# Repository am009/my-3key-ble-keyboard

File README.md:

# 3key-bluetooth-mechanical-keyboard

Based on a tiny esp32 board TTGO T-Display. Draw a simple extension PCB with key switches for it. Connect with two row pins, and put battery in between.

基于TTGO T-Display这个小巧的开发板，通过排针排母连接一个带机械键盘轴的PCB，正好中间的位置放电池。本来打算放四个键，不太放得下就砍掉了一个键。

本项目的目的是学习使用Kicad，尝试画PCB，同时满足自己对小巧的蓝牙键盘的需求。没想到PCB双层板打样这么便宜，5块钱5张，那还用什么洞洞板，飞什么线，自己画拓展板去。这次拓展接线完全就是简单的IO口接轴接GND，甚至用esp32的内部上拉，走线甚至只用了单面。本来想尝试尝试esp_idf开发的，最后还是选择了Arduino IDE。。。比较简单。

Update:
 
- 休眠前主动断开连接，不必等到超时才断开 - ok
- 电量显示有时不稳定，会显示电量为0% - ok
- 低电量闪烁提醒。- 没有合适的板载led

## Reason
背anki用。三个键分别是Enter（good 绿色按钮）数字键1 (again 红色) 数字键2 (hard 灰色)
Make a small ble keyboard for Anki flashcards.
I mount my phone over my pillow, thinking about some way to control my phone. I tried using my Logitech bluethooth keyboard and feel great. When using Ankidroid to remember vocabularies, I found myself needing a tiny bluetooth keyboard.
the three key is set to Enter(for pressing the green(good) button), num 1(for red(again) button), and num 2(for gray(hard) button).

## Hardware

物料：

1. 电池最后选了~~802040（8mm厚，20mmx40mm） 800mah，勉强塞下~~(update 2021.9.13 前两天电池被键轴焊脚戳破了，改用602040锂电池)。续航能力7-10天。是1.25mm 2P 正向接口。 15元两个包邮
2. 买了4个cherry 茶轴和4个灰色键帽。 带邮费26。
3. TTGO T-Display 47元（带排针），加两个12P排母。
4. 自备烙铁焊锡丝。

能够自定义三个键，暂不支持复杂的宏操作。

TTGO自带的按键一个设置为查看电量，一个设置为休眠和开机。

可以自定义蓝牙显示的名称，能够通过蓝牙显示电量信息。

打样打了5块，只用了一块，可以联系我。

唤醒方面原本是通过三个键同时按下唤醒的，最后还是改成了屏幕下方的按钮休眠。

## PCB

PCB设计使用Kicad. 用了下面的组件

[tmk - keyboard_parts](https://github.com/tmk/keyboard_parts.pretty) 键轴

[ttgo_esp32](https://github.com/BravoRoot/ttgo-tdisplay-kicad) for ttgo t-display component.

[MX_Alps_Hybrid](https://github.com/ai03-2725/MX_Alps_Hybrid) 键轴

[ttgo t-display 3d model](https://grabcad.com/library/lilygo-ttgo-t-display-esp32-1) 可以测量尺寸

画PCB的时候为了保险就留了上拉电阻的位置，最后确实不用接。

## Firmware

最后选择了Arduino IDE开发。安装：

1. [Arduino 蓝牙键盘库](https://github.com/T-vK/ESP32-BLE-Keyboard) 
2. [TTGO的屏幕支持库](https://github.com/Xinyuan-LilyGO/TTGO-T-Display) 
3. 按照`Three_Key_TTGO\BleKeyboard.cpp.patch`和`Three_Key_TTGO\BleKeyboard.h.patch`修改ESP32-BLE-Keyboard库(为了支持即时断开连接)

开发板选择 ESP32 Dev Module,在PSRAM选项中选择Disable， Flash Size 选项中选择4MB ，其它保持默认

## TODO

1. 还是有外部上拉比较好，deep-sleep模式下负责内部上拉的RTC外设部分就可以休眠了。

## 图片展示

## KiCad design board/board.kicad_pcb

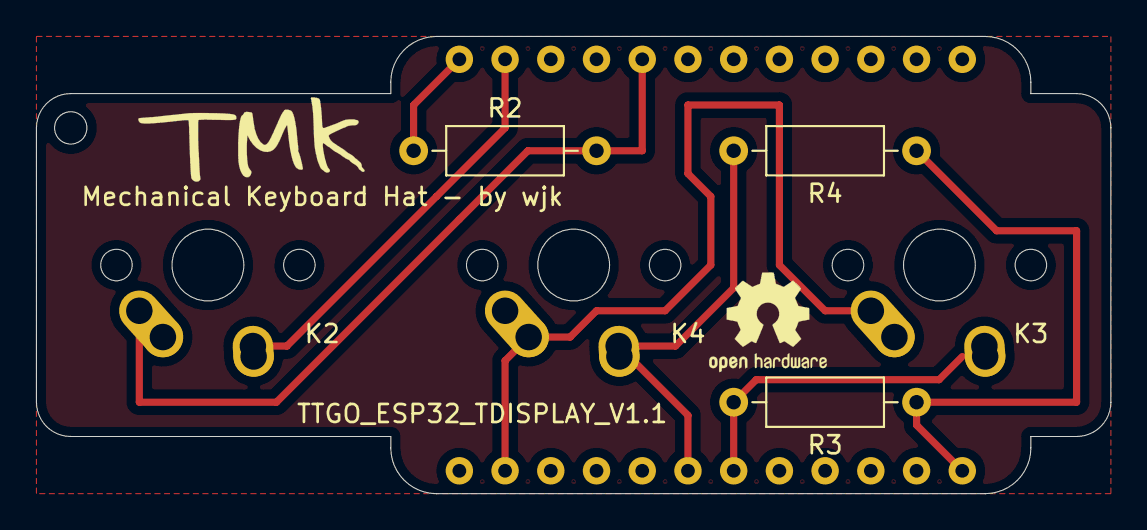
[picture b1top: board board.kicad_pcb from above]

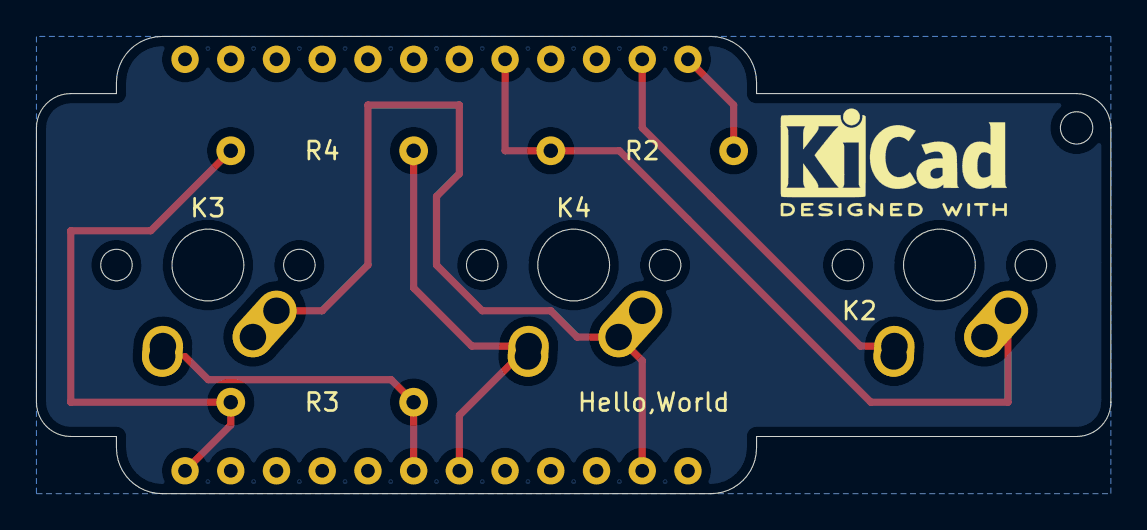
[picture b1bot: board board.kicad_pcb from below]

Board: 2 copper layers, 59.7 x 25.4 mm, 7 parts (3 on the bottom side), 7 nets.

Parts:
K2, K3, K4: KEYSW; MX-1U-NoLED
R2, R3, R4: R; R_Axial_DIN0207_L6.3mm_D2.5mm_P10.16mm_Horizontal
TTGO1: TTGO_ESP32_TDISPLAY_V1.1; TTGO_ESP32_TDisplay_v1.1

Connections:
unnamed: K2.2, TTGO1.23
unnamed: K2.1, R2.2, TTGO1.20
unnamed: K3.1, K4.1, TTGO1.2
unnamed: K3.2, R3.2, TTGO1.7
unnamed: K4.2, R4.2, TTGO1.6
unnamed: R2.1, TTGO1.24
unnamed: R3.1, R4.1, TTGO1.12

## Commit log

2021-02-09 first commit.
2021-02-09 Add geogebra voltage to battery percentage file.
2021-02-23 Disconnect instantly when entering sleep.
2021-02-23 Update reason part of readme.md.
2021-02-27 Fix unstable battery percentage.
2021-03-15 Unstable battery voltage finally fixed. Update setup section in readme.
2021-04-16 Debugging wakeup problem.
2021-04-16 Update dev log: note.md.
2021-09-13 Update README.md
    Update battery info.
2022-03-27 API changed for xTimerResetFromISR?
